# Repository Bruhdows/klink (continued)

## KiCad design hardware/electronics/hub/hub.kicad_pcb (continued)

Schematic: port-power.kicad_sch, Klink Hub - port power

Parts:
C100, C101, C102: 1uF 50V; C_0805_2012Metric; MPN C2012X7R1H105K125AB
C103: 22nF 50V C0G; C_TDK_C2012_Reflow; MPN C2012C0G1H223J125AA
C104: 100nF 50V X7R; C_0805_2012Metric; MPN C2012X7R1H104K125AE
D100: SMBJ22A-E3/52; D_SMB; MPN SMBJ22A-E3/52
Q10: CSD19537Q3; CSD19537Q3_TI; MPN CSD19537Q3
Q11: BSS138LT1G; SOT-23; MPN BSS138LT1G
R100: 10m 1% 1W; R_Vishay_WSL2512_10m; MPN WSL2512R0100FEA
R101, R106, R108: 10k 0.1%; R_0805_2012Metric; MPN TNPW080510K0BEEA
R102: 3k 0.1%; R_0805_2012Metric; MPN TNPW08053K00BEEA
R103, R104: 22k 1%; R_0805_2012Metric; MPN RC0805FR-0722KL
R105: 130k 0.1%; R_0805_2012Metric; MPN TNPW0805130KBEEA
R107: 172k 0.1%; R_0805_2012Metric; MPN TNPW0805172KBEEA
R109: 10k 1%; R_0805_2012Metric; MPN RC0805FR-0710KL
R110: 10k 1% 0.25W; R_1206_3216Metric; MPN RC1206FR0710KL
U20: TPS26630RGER; Texas_RGE0024H_VQFN-24-1EP_4x4mm_P0.5mm_EP2.7x2.7mm_Thermal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; MPN TPS26630RGER
U21: INA301A1IDGKR; VSSOP-8_3x3mm_P0.65mm; MPN INA301A1IDGKR

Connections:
/Distribution/PORT1_20V: C102.1, D100.1 (K), R105.1, R110.1, U20.17 (OUT), U20.18 (OUT); also elsewhere on the board
/Distribution/Port 1/B_DRV: Q11.1 (G), U20.4 (DRV)
/Distribution/Port 1/B_GATE: Q10.4 (G), Q11.3 (D), U20.3 (B_GATE)
/Distribution/Port 1/EFUSE_IN: C101.1, Q10.5 (D), U20.1 (IN), U20.2 (IN)
/Distribution/Port 1/PORT_DVDT: C103.1, U20.9 (dVdT)
/Distribution/Port 1/PORT_ILIM: R102.1, U20.10 (ILIM)
/Distribution/Port 1/PORT_IN: C100.1, Q10.1 (S), Q10.2 (S), Q10.3 (S), Q11.2 (S), R100.2, R107.1, U20.5 (IN_SYS), U21.7 (IN-)
/Distribution/Port 1/PORT_LIMIT: R101.1, U21.3 (LIMIT)
/Distribution/Port 1/PORT_OVP: R107.2, R108.1, U20.7 (OVP)
/Distribution/Port 1/PORT_PGTH: R105.2, R106.1, U20.15 (PGTH)
/INPUT_ENABLE: R109.1, U20.12 (~SHDN); also elsewhere on the board
CONTROL_3V3: C104.1, R103.1, R104.1, U21.1 (VS); also elsewhere on the board
CONTROL_GOOD: U21.5 (RESET); also elsewhere on the board
GND: C100.2, C101.2, C102.2, C103.2, C104.2, D100.2 (A), R101.2, R102.2, R106.2, R108.2, R109.2, R110.2, U20.6 (UVLO), U20.8 (GND), U20.25 (GND), U21.4 (GND); also elsewhere on the board
HUB_20V: R100.1, U21.8 (IN+); also elsewhere on the board
PORT1_HEALTH_N: R104.2, U20.14 (~FLT), U20.16 (PGOOD); also elsewhere on the board
PORT1_MON: U21.2 (OUT); also elsewhere on the board
PORT1_OC_N: R103.2, U21.6 (~ALERT); also elsewhere on the board

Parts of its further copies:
C110, C111, C112, C120, C121, C122, C130, C131, C132, C140, C141, C142, C150, C151, C152: 1uF 50V; C_0805_2012Metric; MPN C2012X7R1H105K125AB
C113, C123, C133, C143, C153: 22nF 50V C0G; C_TDK_C2012_Reflow; MPN C2012C0G1H223J125AA
C114, C124, C134, C144, C154: 100nF 50V X7R; C_0805_2012Metric; MPN C2012X7R1H104K125AE
D101, D102, D103, D104, D105: SMBJ22A-E3/52; D_SMB; MPN SMBJ22A-E3/52
Q12, Q14, Q16, Q18, Q20: CSD19537Q3; CSD19537Q3_TI; MPN CSD19537Q3
Q13, Q15, Q17, Q19, Q21: BSS138LT1G; SOT-23; MPN BSS138LT1G
R120, R140, R160, R180, R200: 10m 1% 1W; R_Vishay_WSL2512_10m; MPN WSL2512R0100FEA
R121, R126, R128, R141, R146, R148, R161, R166, R168, R181, R186, R188, R201, R206, R208: 10k 0.1%; R_0805_2012Metric; MPN TNPW080510K0BEEA
R122, R142, R162, R182, R202: 3k 0.1%; R_0805_2012Metric; MPN TNPW08053K00BEEA
R123, R124, R143, R144, R163, R164, R183, R184, R203, R204: 22k 1%; R_0805_2012Metric; MPN RC0805FR-0722KL
R125, R145, R165, R185, R205: 130k 0.1%; R_0805_2012Metric; MPN TNPW0805130KBEEA
R127, R147, R167, R187, R207: 172k 0.1%; R_0805_2012Metric; MPN TNPW0805172KBEEA
R129, R149, R169, R189, R209: 10k 1%; R_0805_2012Metric; MPN RC0805FR-0710KL
R130, R150, R170, R190, R210: 10k 1% 0.25W; R_1206_3216Metric; MPN RC1206FR0710KL
U22, U24, U26, U28, U30: TPS26630RGER; Texas_RGE0024H_VQFN-24-1EP_4x4mm_P0.5mm_EP2.7x2.7mm_Thermal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; MPN TPS26630RGER
U23, U25, U27, U29, U31: INA301A1IDGKR; VSSOP-8_3x3mm_P0.65mm; MPN INA301A1IDGKR

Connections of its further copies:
/Distribution/PORT2_20V: C112.1, D101.1 (K), R125.1, R130.1, U22.17 (OUT), U22.18 (OUT); also elsewhere on the board
/Distribution/PORT3_20V: C122.1, D102.1 (K), R145.1, R150.1, U24.17 (OUT), U24.18 (OUT); also elsewhere on the board
/Distribution/PORT4_20V: C132.1, D103.1 (K), R165.1, R170.1, U26.17 (OUT), U26.18 (OUT); also elsewhere on the board
/Distribution/PORT5_20V: C142.1, D104.1 (K), R185.1, R190.1, U28.17 (OUT), U28.18 (OUT); also elsewhere on the board
/Distribution/PORT6_20V: C152.1, D105.1 (K), R205.1, R210.1, U30.17 (OUT), U30.18 (OUT); also elsewhere on the board
/Distribution/Port 2/B_DRV: Q13.1 (G), U22.4 (DRV)
/Distribution/Port 2/B_GATE: Q12.4 (G), Q13.3 (D), U22.3 (B_GATE)
/Distribution/Port 2/EFUSE_IN: C111.1, Q12.5 (D), U22.1 (IN), U22.2 (IN)
/Distribution/Port 2/PORT_DVDT: C113.1, U22.9 (dVdT)
/Distribution/Port 2/PORT_ILIM: R122.1, U22.10 (ILIM)
/Distribution/Port 2/PORT_IN: C110.1, Q12.1 (S), Q12.2 (S), Q12.3 (S), Q13.2 (S), R120.2, R127.1, U22.5 (IN_SYS), U23.7 (IN-)
/Distribution/Port 2/PORT_LIMIT: R121.1, U23.3 (LIMIT)
/Distribution/Port 2/PORT_OVP: R127.2, R128.1, U22.7 (OVP)
/Distribution/Port 2/PORT_PGTH: R125.2, R126.1, U22.15 (PGTH)
/Distribution/Port 3/B_DRV: Q15.1 (G), U24.4 (DRV)
/Distribution/Port 3/B_GATE: Q14.4 (G), Q15.3 (D), U24.3 (B_GATE)
/Distribution/Port 3/EFUSE_IN: C121.1, Q14.5 (D), U24.1 (IN), U24.2 (IN)
/Distribution/Port 3/PORT_DVDT: C123.1, U24.9 (dVdT)
/Distribution/Port 3/PORT_ILIM: R142.1, U24.10 (ILIM)
/Distribution/Port 3/PORT_IN: C120.1, Q14.1 (S), Q14.2 (S), Q14.3 (S), Q15.2 (S), R140.2, R147.1, U24.5 (IN_SYS), U25.7 (IN-)
/Distribution/Port 3/PORT_LIMIT: R141.1, U25.3 (LIMIT)
/Distribution/Port 3/PORT_OVP: R147.2, R148.1, U24.7 (OVP)
/Distribution/Port 3/PORT_PGTH: R145.2, R146.1, U24.15 (PGTH)
/Distribution/Port 4/B_DRV: Q17.1 (G), U26.4 (DRV)
/Distribution/Port 4/B_GATE: Q16.4 (G), Q17.3 (D), U26.3 (B_GATE)
/Distribution/Port 4/EFUSE_IN: C131.1, Q16.5 (D), U26.1 (IN), U26.2 (IN)
/Distribution/Port 4/PORT_DVDT: C133.1, U26.9 (dVdT)
/Distribution/Port 4/PORT_ILIM: R162.1, U26.10 (ILIM)
/Distribution/Port 4/PORT_IN: C130.1, Q16.1 (S), Q16.2 (S), Q16.3 (S), Q17.2 (S), R160.2, R167.1, U26.5 (IN_SYS), U27.7 (IN-)
/Distribution/Port 4/PORT_LIMIT: R161.1, U27.3 (LIMIT)
/Distribution/Port 4/PORT_OVP: R167.2, R168.1, U26.7 (OVP)
/Distribution/Port 4/PORT_PGTH: R165.2, R166.1, U26.15 (PGTH)
/Distribution/Port 5/B_DRV: Q19.1 (G), U28.4 (DRV)
/Distribution/Port 5/B_GATE: Q18.4 (G), Q19.3 (D), U28.3 (B_GATE)
/Distribution/Port 5/EFUSE_IN: C141.1, Q18.5 (D), U28.1 (IN), U28.2 (IN)
/Distribution/Port 5/PORT_DVDT: C143.1, U28.9 (dVdT)
/Distribution/Port 5/PORT_ILIM: R182.1, U28.10 (ILIM)
/Distribution/Port 5/PORT_IN: C140.1, Q18.1 (S), Q18.2 (S), Q18.3 (S), Q19.2 (S), R180.2, R187.1, U28.5 (IN_SYS), U29.7 (IN-)
/Distribution/Port 5/PORT_LIMIT: R181.1, U29.3 (LIMIT)
/Distribution/Port 5/PORT_OVP: R187.2, R188.1, U28.7 (OVP)
/Distribution/Port 5/PORT_PGTH: R185.2, R186.1, U28.15 (PGTH)
/Distribution/Port 6/B_DRV: Q21.1 (G), U30.4 (DRV)
/Distribution/Port 6/B_GATE: Q20.4 (G), Q21.3 (D), U30.3 (B_GATE)
/Distribution/Port 6/EFUSE_IN: C151.1, Q20.5 (D), U30.1 (IN), U30.2 (IN)
/Distribution/Port 6/PORT_DVDT: C153.1, U30.9 (dVdT)
/Distribution/Port 6/PORT_ILIM: R202.1, U30.10 (ILIM)
/Distribution/Port 6/PORT_IN: C150.1, Q20.1 (S), Q20.2 (S), Q20.3 (S), Q21.2 (S), R200.2, R207.1, U30.5 (IN_SYS), U31.7 (IN-)
/Distribution/Port 6/PORT_LIMIT: R201.1, U31.3 (LIMIT)
/Distribution/Port 6/PORT_OVP: R207.2, R208.1, U30.7 (OVP)
/Distribution/Port 6/PORT_PGTH: R205.2, R206.1, U30.15 (PGTH)
/INPUT_ENABLE: R129.1, R149.1, R169.1, R189.1, R209.1, U22.12 (~SHDN), U24.12 (~SHDN), U26.12 (~SHDN), U28.12 (~SHDN), U30.12 (~SHDN); also elsewhere on the board
CONTROL_3V3: C114.1, C124.1, C134.1, C144.1, C154.1, R123.1, R124.1, R143.1, R144.1, R163.1, R164.1, R183.1, R184.1, R203.1, R204.1, U23.1 (VS), U25.1 (VS), U27.1 (VS), U29.1 (VS), U31.1 (VS); also elsewhere on the board
CONTROL_GOOD: U23.5 (RESET), U25.5 (RESET), U27.5 (RESET), U29.5 (RESET), U31.5 (RESET); also elsewhere on the board
GND: C110.2, C111.2, C112.2, C113.2, C114.2, C120.2, C121.2, C122.2, C123.2, C124.2, C130.2, C131.2, C132.2, C133.2, C134.2, C140.2, C141.2, C142.2, C143.2, C144.2, C150.2, C151.2, C152.2, C153.2, C154.2, D101.2 (A), D102.2 (A), D103.2 (A), D104.2 (A), D105.2 (A), R121.2, R122.2, R126.2, R128.2, R129.2, R130.2, R141.2, R142.2, R146.2, R148.2, R149.2, R150.2, R161.2, R162.2, R166.2, R168.2, R169.2, R170.2, R181.2, R182.2, R186.2, R188.2, R189.2, R190.2, R201.2, R202.2, R206.2, R208.2, R209.2, R210.2, U22.6 (UVLO), U22.8 (GND), U22.25 (GND), U23.4 (GND), U24.6 (UVLO), U24.8 (GND), U24.25 (GND), U25.4 (GND), U26.6 (UVLO), U26.8 (GND), U26.25 (GND), U27.4 (GND), U28.6 (UVLO), U28.8 (GND), U28.25 (GND), U29.4 (GND), U30.6 (UVLO), U30.8 (GND), U30.25 (GND), U31.4 (GND); also elsewhere on the board
HUB_20V: R120.1, R140.1, R160.1, R180.1, R200.1, U23.8 (IN+), U25.8 (IN+), U27.8 (IN+), U29.8 (IN+), U31.8 (IN+); also elsewhere on the board
PORT2_HEALTH_N: R124.2, U22.14 (~FLT), U22.16 (PGOOD); also elsewhere on the board
PORT2_MON: U23.2 (OUT); also elsewhere on the board
PORT2_OC_N: R123.2, U23.6 (~ALERT); also elsewhere on the board
PORT3_HEALTH_N: R144.2, U24.14 (~FLT), U24.16 (PGOOD); also elsewhere on the board
PORT3_MON: U25.2 (OUT); also elsewhere on the board
PORT3_OC_N: R143.2, U25.6 (~ALERT); also elsewhere on the board
PORT4_HEALTH_N: R164.2, U26.14 (~FLT), U26.16 (PGOOD); also elsewhere on the board
PORT4_MON: U27.2 (OUT); also elsewhere on the board
PORT4_OC_N: R163.2, U27.6 (~ALERT); also elsewhere on the board
PORT5_HEALTH_N: R184.2, U28.14 (~FLT), U28.16 (PGOOD); also elsewhere on the board
PORT5_MON: U29.2 (OUT); also elsewhere on the board
PORT5_OC_N: R183.2, U29.6 (~ALERT); also elsewhere on the board
PORT6_HEALTH_N: R204.2, U30.14 (~FLT), U30.16 (PGOOD); also elsewhere on the board
PORT6_MON: U31.2 (OUT); also elsewhere on the board
PORT6_OC_N: R203.2, U31.6 (~ALERT); also elsewhere on the board

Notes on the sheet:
Kelvin route R100. Nominal trip 4A; all ports latch off on a fault.
C100-C102 require at least 0.1uF effective capacitance at 21V.
TVS clamp is 35.5V at 16.9A, 25C. Hot-pulse coordination remains unqualified.

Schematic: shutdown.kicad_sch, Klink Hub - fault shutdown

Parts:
C300, C303, C306, C307, C308, C309, C310, C311, C312, C313: 100nF 50V X7R; C_0805_2012Metric; MPN C2012X7R1H104K125AE
R302: 22k 1%; R_0805_2012Metric; MPN RC0805FR-0722KL
R303: 100k 1%; R_0805_2012Metric; MPN RC0805FR-07100KL
R304: 47k 1%; R_0805_2012Metric; MPN RC0805FR-0747KL
TP30: FAULT_LATCHED; TestPoint_Pad_D2.0mm
TP31: ARMED; TestPoint_Pad_D2.0mm
U40, U43: SN74HCS11PWR; TSSOP-14_4.4x5mm_P0.65mm; MPN SN74HCS11PWR
U46, U48: SN74LVC1G32DBVR; SOT-23-5; MPN SN74LVC1G32DBVR
U47: SN74LVC1G08DBVR; SOT-23-5; MPN SN74LVC1G08DBVR
U49: SN74LVC1G04DBVR; SOT-23-5; MPN SN74LVC1G04DBVR
U50: SN74LVC74APWR; TSSOP-14_4.4x5mm_P0.65mm; MPN SN74LVC74APWR
U51, U53: SN74LVC2G17DBVR; SOT-23-6; MPN SN74LVC2G17DBVR
U52: TPS3808G01DBVR; SOT-23-6; MPN TPS3808G01DBVR

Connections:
/CONTROL_GOOD_RAW: U51.3; also elsewhere on the board
/Distribution/Fault shutdown/ALL_HEALTH_N: U46.1, U53.4
/Distribution/Fault shutdown/ALL_HEALTH_RAW_N: U43.8, U53.3
/Distribution/Fault shutdown/ALL_OC_N: U47.1, U53.6
/Distribution/Fault shutdown/ALL_OC_RAW_N: U40.8, U53.1
/Distribution/Fault shutdown/ARM_N: U46.2, U50.8 (~Q)
/Distribution/Fault shutdown/CONTROL_GOOD_N: U48.2, U49.4
/Distribution/Fault shutdown/FAULT_SET_N: U48.4, U50.4 (~S)
/Distribution/Fault shutdown/FAULT_SOURCE_N: U47.4, U48.1
/Distribution/Fault shutdown/HEALTH_A: U43.9, U43.12
/Distribution/Fault shutdown/HEALTH_B: U43.6, U43.10
/Distribution/Fault shutdown/HEALTH_READY_N: U46.4, U47.2
/Distribution/Fault shutdown/OC_A: U40.9, U40.12
/Distribution/Fault shutdown/OC_B: U40.6, U40.10
/Distribution/Fault shutdown/START_CT: R303.2, U52.4 (CT)
/Distribution/Fault shutdown/START_DONE: U50.11 (C), U51.6
/Distribution/Fault shutdown/START_DONE_RAW: R302.2, U51.1, U52.1 (~RESET)
/INPUT_ENABLE: U52.5 (SENSE); also elsewhere on the board
/RUN_OK: R304.1, U50.6 (~Q); also elsewhere on the board
ARMED: TP31.1, U50.9 (Q); also elsewhere on the board
CONTROL_3V3: C300.1, C303.1, C306.1, C307.1, C308.1, C309.1, C310.1, C311.1, C312.1, C313.1, R302.1, R303.1, U40.14 (VCC), U43.14 (VCC), U46.5 (VCC), U47.5 (VCC), U48.5 (VCC), U49.5 (VCC), U50.10 (~S), U50.12 (D), U50.14 (VCC), U51.5 (VCC), U52.6 (VDD), U53.5 (VCC); also elsewhere on the board
CONTROL_GOOD: U49.2, U50.1 (~R), U50.13 (~R), U51.4, U52.3 (~MR); also elsewhere on the board
FAULT_LATCHED: TP30.1, U50.5 (Q); also elsewhere on the board
GND: C300.2, C303.2, C306.2, C307.2, C308.2, C309.2, C310.2, C311.2, C312.2, C313.2, R304.2, U40.7 (GND), U43.7 (GND), U46.3 (GND), U47.3 (GND), U48.3 (GND), U49.3 (GND), U50.2 (D), U50.3 (C), U50.7 (GND), U51.2 (GND), U52.2 (GND), U53.2 (GND); also elsewhere on the board
INPUT_FAULT_N: U43.11; also elsewhere on the board
INPUT_OC_N: U40.11; also elsewhere on the board
PORT1_HEALTH_N: U43.1; also elsewhere on the board
PORT1_OC_N: U40.1; also elsewhere on the board
PORT2_HEALTH_N: U43.2; also elsewhere on the board
PORT2_OC_N: U40.2; also elsewhere on the board
PORT3_HEALTH_N: U43.13; also elsewhere on the board
PORT3_OC_N: U40.13; also elsewhere on the board
PORT4_HEALTH_N: U43.3; also elsewhere on the board
PORT4_OC_N: U40.3; also elsewhere on the board
PORT5_HEALTH_N: U43.4; also elsewhere on the board
PORT5_OC_N: U40.4; also elsewhere on the board
PORT6_HEALTH_N: U43.5; also elsewhere on the board
PORT6_OC_N: U40.5; also elsewhere on the board

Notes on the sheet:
Overcurrent is never blanked. Health faults latch when the startup allowance expires.
CT to VDD through 100k: 180-420ms allowance from the power-enable request.

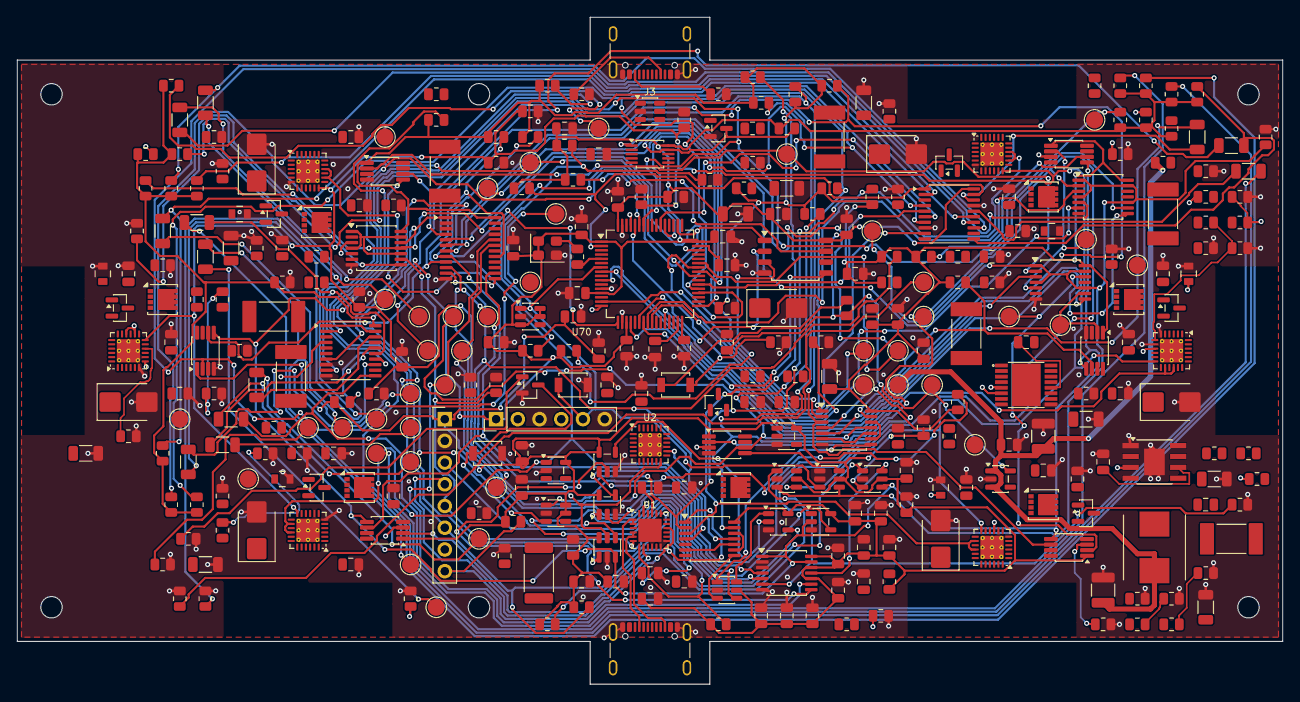
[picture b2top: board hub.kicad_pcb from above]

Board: 4 copper layers, 148.0 x 78.0 mm, 356 parts (0 on the bottom side), 227 nets.

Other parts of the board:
H1, H2, H3, H4, H5, H6: MountingHole_2.5mm

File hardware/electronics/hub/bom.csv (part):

Reference,Value,MPN,Alternate,TCR,Footprint,Quantity,purchase_url,unit_price,currency,price_status,checked_date,lcsc_reference
C1,1uF 50V,C2012X7R1H105K125AB,,,Capacitor_SMD:C_0805_2012Metric,1,https://www.mouser.com/ProductDetail/TDK/C2012X7R1H105K125AB,0.1,USD,engineering allowance; NOT a verified supplier price,,
C2,1uF 10V,C2012X7R1H105K125AB,,,Capacitor_SMD:C_0805_2012Metric,1,https://www.mouser.com/ProductDetail/TDK/C2012X7R1H105K125AB,0.1,USD,engineering allowance; NOT a verified supplier price,,
C3,1uF 10V,C2012X7R1H105K125AB,,,Capacitor_SMD:C_0805_2012Metric,1,https://www.mouser.com/ProductDetail/TDK/C2012X7R1H105K125AB,0.1,USD,engineering allowance; NOT a verified supplier price,,
C4,100nF 50V X7R,C2012X7R1H104K125AE,,,Capacitor_SMD:C_0805_2012Metric,1,https://www.mouser.com/ProductDetail/TDK/C2012X7R1H104K125AE,0.1,USD,engineering allowance; NOT a verified supplier price,,
J1,USB4105-GF-A,USB4105-GF-A,,,Klink:USB_C_Receptacle_GCT_USB4105_RoundedGround,1,https://www.mouser.com/ProductDetail/GCT/USB4105-GF-A,0.9,USD,engineering allowance; NOT a verified supplier price,,
J2,PD_SERVICE,TSW-108-07-G-S,,,Connector_PinHeader_2.54mm:PinHeader_1x08_P2.54mm_Vertical,1,https://www.mouser.com/ProductDetail/Samtec/TSW-108-07-G-S,0.7,USD,engineering allowance; NOT a verified supplier price,,
R1,470 1% 2W,RC2512FK-7W470RL,,,Resistor_SMD:R_2512_6332Metric,1,https://www.mouser.com/ProductDetail/Yageo/RC2512FK-7W470RL,0.1,USD,engineering allowance; NOT a verified supplier price,,
R2,10k 1%,RC0805FR-0710KL,,,Resistor_SMD:R_0805_2012Metric,1,https://www.lcsc.com/product-detail/C84376.html,0.0049,USD,supplier reference listing; not a quote,2026-11-08,C84376
R3,4.7k 1%,RC0805FR-074K7L,,,Resistor_SMD:R_0805_2012Metric,1,https://www.mouser.com/ProductDetail/Yageo/RC0805FR-074K7L,0.04,USD,engineering allowance; NOT a verified supplier price,,
R4,4.7k 1%,RC0805FR-074K7L,,,Resistor_SMD:R_0805_2012Metric,1,https://www.mouser.com/ProductDetail/Yageo/RC0805FR-074K7L,0.04,USD,engineering allowance; NOT a verified supplier price,,
R5,4.7k 1%,RC0805FR-074K7L,,,Resistor_SMD:R_0805_2012Metric,1,https://www.mouser.com/ProductDetail/Yageo/RC0805FR-074K7L,0.04,USD,engineering allowance; NOT a verified supplier price,,
R6,10k 1%,RC0805FR-0710KL,,,Resistor_SMD:R_0805_2012Metric,1,https://www.lcsc.com/product-detail/C84376.html,0.0049,USD,supplier reference listing; not a quote,2026-11-08,C84376
R7,10k 1%,RC0805FR-0710KL,,,Resistor_SMD:R_0805_2012Metric,1,https://www.lcsc.com/product-detail/C84376.html,0.0049,USD,supplier reference listing; not a quote,2026-11-08,C84376
U1,STUSB4500QTR,STUSB4500QTR,,,Package_DFN_QFN:QFN-24-1EP_4x4mm_P0.5mm_EP2.7x2.7mm,1,https://www.mouser.com/ProductDetail/STMicroelectronics/STUS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,3,USD,engineering allowance; NOT a verified supplier price,,
C5,100nF 50V X7R,C2012X7R1H104K125AE,,,Capacitor_SMD:C_0805_2012Metric,1,https://www.mouser.com/ProductDetail/TDK/C2012X7R1H104K125AE,0.1,USD,engineering allowance; NOT a verified supplier price,,
C6,1uF 50V,C2012X7R1H105K125AB,,,Capacitor_SMD:C_0805_2012Metric,1,https://www.mouser.com/ProductDetail/TDK/C2012X7R1H105K125AB,0.1,USD,engineering allowance; NOT a verified supplier price,,
C7,100nF 50V X7R,C2012X7R1H104K125AE,,,Capacitor_SMD:C_0805_2012Metric,1,https://www.mouser.com/ProductDetail/TDK/C2012X7R1H104K125AE,0.1,USD,engineering allowance; NOT a verified supplier price,,
C8,100nF 50V,C2012X7R1H104K125AE,,,Capacitor_SMD:C_0805_2012Metric,1,https://www.mouser.com/ProductDetail/TDK/C2012X7R1H104K125AE,0.1,USD,engineering allowance; NOT a verified supplier price,,
C9,10uF 50V X7R,C3216X7R1H106K160AC,,,Capacitor_SMD:C_1206_3216Metric,1,https://www.mouser.com/ProductDetail/TDK/C3216X7R1H106K160AC,0.35,USD,engineering allowance; NOT a verified supplier price,,
C10,100nF 50V X7R,C2012X7R1H104K125AE,,,Capacitor_SMD:C_0805_2012Metric,1,https://www.mouser.com/ProductDetail/TDK/C2012X7R1H104K125AE,0.1,USD,engineering allowance; NOT a verified supplier price,,
C11,100nF 50V X7R,C2012X7R1H104K125AE,,,Capacitor_SMD:C_0805_2012Metric,1,https://www.mouser.com/ProductDetail/TDK/C2012X7R1H104K125AE,0.1,USD,engineering allowance; NOT a verified supplier price,,
C12,100nF 50V X7R,C2012X7R1H104K125AE,,,Capacitor_SMD:C_0805_2012Metric,1,https://www.mouser.com/ProductDetail/TDK/C2012X7R1H104K125AE,0.1,USD,engineering allowance; NOT a verified supplier price,,
C13,100nF 50V X7R,C2012X7R1H104K125AE,,,Capacitor_SMD:C_0805_2012Metric,1,https://www.mouser.com/ProductDetail/TDK/C2012X7R1H104K125AE,0.1,USD,engineering allowance; NOT a verified supplier price,,
C14,1uF 50V,C2012X7R1H105K125AB,,,Capacitor_SMD:C_0805_2012Metric,1,https://www.mouser.com/ProductDetail/TDK/C2012X7R1H105K125AB,0.1,USD,engineering allowance; NOT a verified supplier price,,
C462,100nF 50V X7R,C2012X7R1H104K125AE,,,Capacitor_SMD:C_0805_2012Metric,1,https://www.mouser.com/ProductDetail/TDK/C2012X7R1H104K125AE,0.1,USD,engineering allowance; NOT a verified supplier price,,
D8,SMBJ22A-E3/52,SMBJ22A-E3/52,,,Diode_SMD:D_SMB,1,https://www.mouser.com/ProductDetail/Vishay/SMBJ22A-E3%2F52,0.35,USD,engineering allowance; NOT a verified supplier price,,
Q1,CSD19537Q3,CSD19537Q3,,,Klink:CSD19537Q3_TI,1,https://www.mouser.com/ProductDetail/Texas-Instruments/CSD19537Q3,1.5,USD,engineering allowance; NOT a verified supplier price,,
Q2,BSS138LT1G,BSS138LT1G,,,Package_TO_SOT_SMD:SOT-23,1,https://www.mouser.com/ProductDetail/onsemi/BSS138LT1G,0.15,USD,engineering allowance; NOT a verified supplier price,,
R8,10m 1% 1W,WSL2512R0100FEA,,,Klink:R_Vishay_WSL2512_10m,1,https://www.mouser.com/ProductDetail/Vishay/WSL2512R0100FEA,0.7,USD,engineering allowance; NOT a verified supplier price,,
R9,135k 0.1%,TNPW0805135KBEEA,,25ppm/K,Resistor_SMD:R_0805_2012Metric,1,https://www.mouser.com/ProductDetail/Vishay/TNPW0805135KBEEA,0.3,USD,engineering allowance; NOT a verified supplier price,,
R10,10k 0.1%,TNPW080510K0BEEA,,25ppm/K,Resistor_SMD:R_0805_2012Metric,1,https://www.mouser.com/ProductDetail/Vishay/TNPW080510K0BEEA,0.3,USD,engineering allowance; NOT a verified supplier price,,
R11,172k 0.1%,TNPW0805172KBEEA,,25ppm/K,Resistor_SMD:R_0805_2012Metric,1,https://www.mouser.com/ProductDetail/Vishay/TNPW0805172KBEEA,0.3,USD,engineering allowance; NOT a verified supplier price,,
R12,10k 0.1%,TNPW080510K0BEEA,,25ppm/K,Resistor_SMD:R_0805_2012Metric,1,https://www.mouser.com/ProductDetail/Vishay/TNPW080510K0BEEA,0.3,USD,engineering allowance; NOT a verified supplier price,,
R13,3k 0.1%,TNPW08053K00BEEA,,25ppm/K,Resistor_SMD:R_0805_2012Metric,1,https://www.mouser.com/ProductDetail/Vishay/TNPW08053K00BEEA,0.3,USD,engineering allowance; NOT a verified supplier price,,
R14,10.5k 0.1%,ERA6AEB1052V,,25ppm/K,Resistor_SMD:R_0805_2012Metric,1,https://www.mouser.com/ProductDetail/Panasonic/ERA6AEB1052V,0.3,USD,engineering allowance; NOT a verified supplier price,,
R15,22k 1%,RC0805FR-0722KL,,,Resistor_SMD:R_0805_2012Metric,1,https://www.mouser.com/ProductDetail/Yageo/RC0805FR-0722KL,0.04,USD,engineering allowance; NOT a verified supplier price,,
R16,10k 1%,RC0805FR-0710KL,,,Resistor_SMD:R_0805_2012Metric,1,https://www.lcsc.com/product-detail/C84376.html,0.0049,USD,supplier reference listing; not a quote,2026-11-08,C84376
R17,10k 1%,RC0805FR-0710KL,,,Resistor_SMD:R_0805_2012Metric,1,https://www.lcsc.com/product-detail/C84376.html,0.0049,USD,supplier reference listing; not a quote,2026-11-08,C84376
R18,10k 1%,RC0805FR-0710KL,,,Resistor_SMD:R_0805_2012Metric,1,https://www.lcsc.com/product-detail/C84376.html,0.0049,USD,supplier reference listing; not a quote,2026-11-08,C84376
R19,22k 1%,RC0805FR-0722KL,,,Resistor_SMD:R_0805_2012Metric,1,https://www.mouser.com/ProductDetail/Yageo/RC0805FR-0722KL,0.04,USD,engineering allowance; NOT a verified supplier price,,
R20,10k 1% 0.25W,RC1206FR0710KL,,,Resistor_SMD:R_1206_3216Metric,1,https://www.mouser.com/ProductDetail/Yageo/RC1206FR0710KL,0.1,USD,engineering allowance; NOT a verified supplier price,,
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
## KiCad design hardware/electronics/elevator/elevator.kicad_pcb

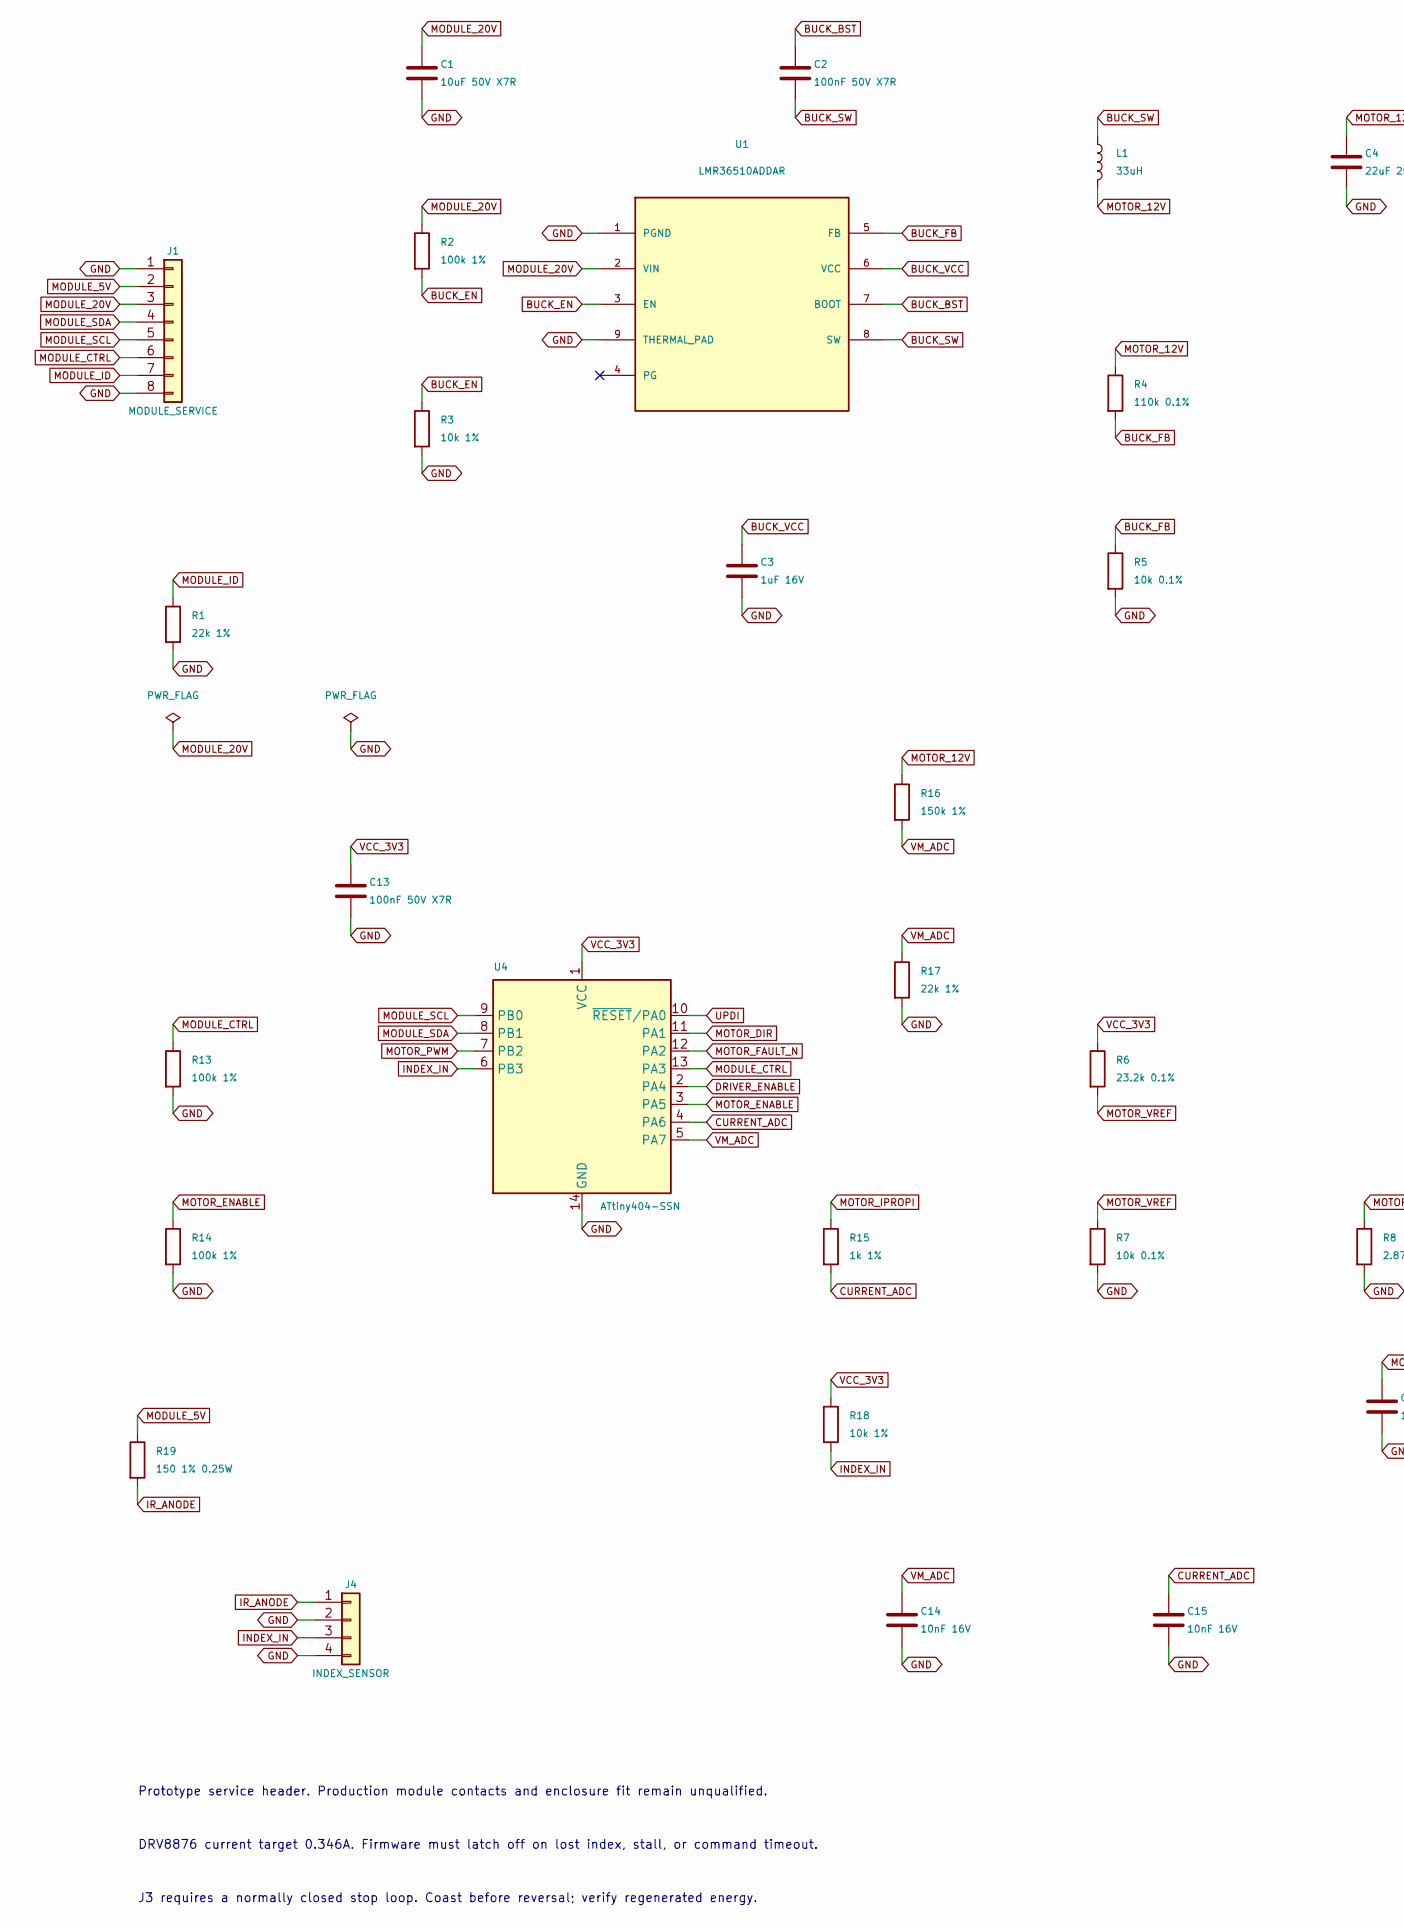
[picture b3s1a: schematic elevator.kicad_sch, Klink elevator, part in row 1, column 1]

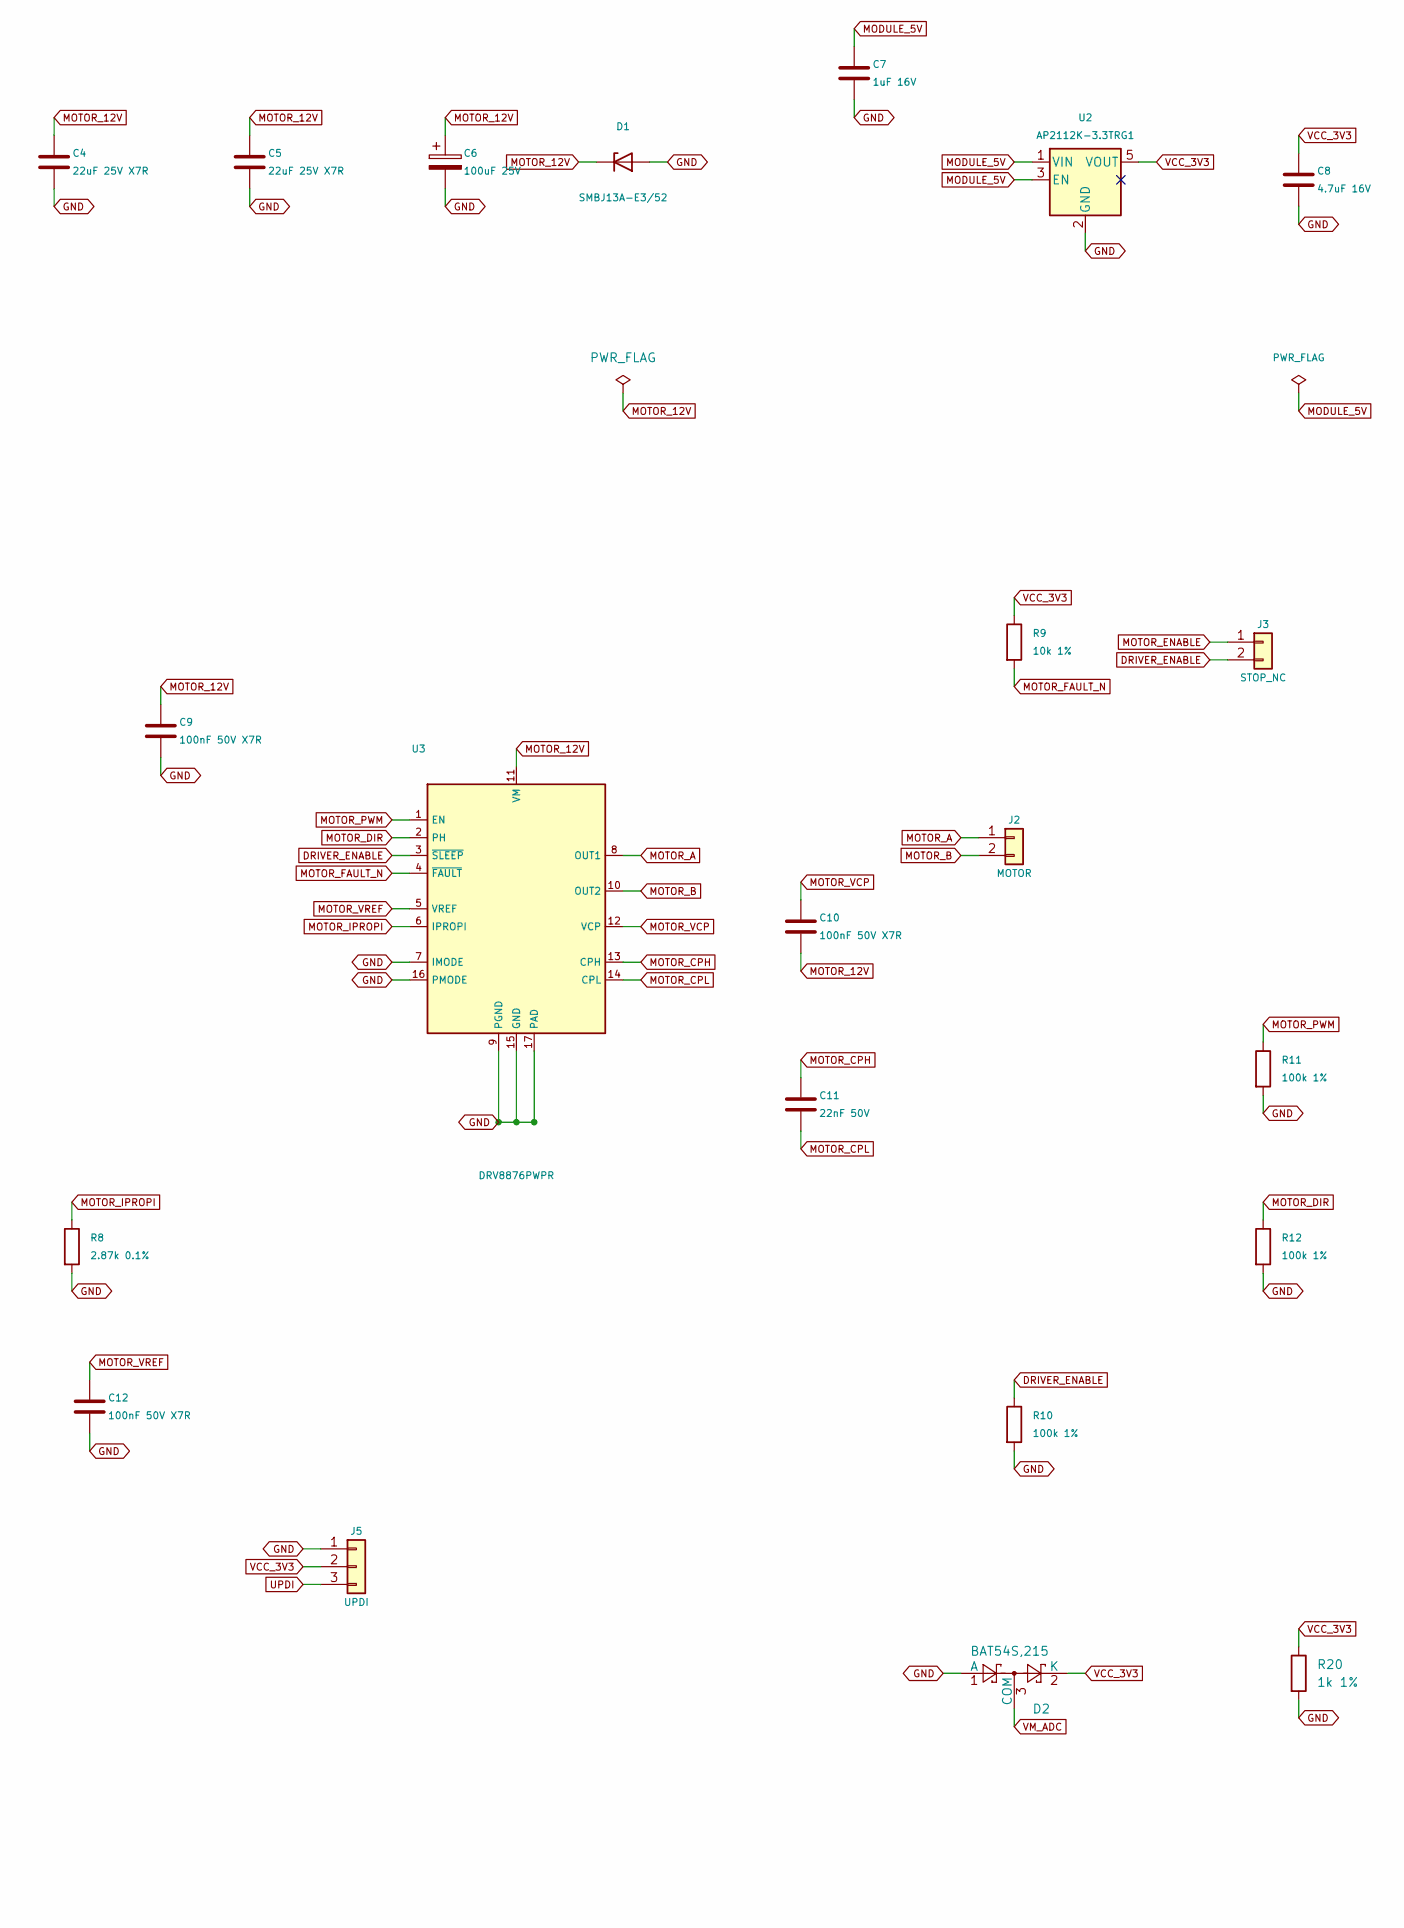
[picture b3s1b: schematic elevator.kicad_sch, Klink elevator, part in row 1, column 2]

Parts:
C1: 10uF 50V X7R; C_1206_3216Metric; MPN C3216X7R1H106K160AC
C2, C9, C10, C12, C13: 100nF 50V X7R; C_0805_2012Metric; MPN C2012X7R1H104K125AE
C3, C7: 1uF 16V; C_0805_2012Metric; MPN C2012X7R1H105K125AB
C4, C5: 22uF 25V X7R; C_1210_3225Metric; MPN C1210C226K3RACTU
C6: 100uF 25V; CP_Elec_6.3x7.7; MPN EEH-ZC1E101XP
C8: 4.7uF 16V; C_0805_2012Metric; MPN C2012X7R1C475K125AB
C11: 22nF 50V; C_TDK_C2012_Reflow; MPN C2012C0G1H223J125AA
C14, C15: 10nF 16V; C_0805_2012Metric; MPN CC0805KRX7R9BB103
D1: SMBJ13A-E3/52; D_SMB; MPN SMBJ13A-E3/52
D2: BAT54S,215; SOT-23; MPN BAT54S,215
J1: MODULE_SERVICE; PinHeader_1x08_P2.54mm_Vertical; MPN TSW-108-07-G-S
J2: MOTOR; PinHeader_1x02_P2.54mm_Vertical; MPN TSW-102-07-G-S
J3: STOP_NC; PinHeader_1x02_P2.54mm_Vertical; MPN TSW-102-07-G-S
J4: INDEX_SENSOR; PinHeader_1x04_P2.54mm_Vertical; MPN TSW-104-07-G-S
J5: UPDI; PinHeader_1x03_P2.54mm_Vertical; MPN TSW-103-07-G-S
L1: 33uH; L_Bourns_SRP7050TA; MPN SRP7050TA-330M
R1, R17: 22k 1%; R_0805_2012Metric; MPN RC0805FR-0722KL
R2, R10, R11, R12, R13, R14: 100k 1%; R_0805_2012Metric; MPN RC0805FR-07100KL
R3, R9, R18: 10k 1%; R_0805_2012Metric; MPN RC0805FR-0710KL
R4: 110k 0.1%; R_0805_2012Metric; MPN RT0805BRD07110KL
R5, R7: 10k 0.1%; R_0805_2012Metric; MPN RT0805BRD0710KL
R6: 23.2k 0.1%; R_0805_2012Metric; MPN RT0805BRD0723K2L
R8: 2.87k 0.1%; R_0805_2012Metric; MPN RT0805BRD072K87L
R15, R20: 1k 1%; R_0805_2012Metric; MPN RC0805FR-071KL
R16: 150k 1%; R_0805_2012Metric; MPN RC0805FR-07150KL
R19: 150 1% 0.25W; R_1206_3216Metric; MPN RC1206FR-07150RL
U1: LMR36510ADDAR; TI_SO-PowerPAD-8; MPN LMR36510ADDAR
U2: AP2112K-3.3TRG1; SOT-23-5; MPN AP2112K-3.3TRG1
U3: DRV8876PWPR; TI_PWP0016A_Mask3.3x3.3; MPN DRV8876PWPR
U4: ATtiny404-SSN; SOIC-14_3.9x8.7mm_P1.27mm; MPN ATTINY404-SSN

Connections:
BUCK_BST: C2.1, U1.7 (BOOT)
BUCK_EN: R2.2, R3.1, U1.3 (EN)
BUCK_FB: R4.2, R5.1, U1.5 (FB)
BUCK_SW: C2.2, L1.1, U1.8 (SW)
BUCK_VCC: C3.1, U1.6 (VCC)
CURRENT_ADC: C15.1, R15.2, U4.4 (PA6)
DRIVER_ENABLE: J3.2, R10.1, U3.3 (~SLEEP), U4.2 (PA4)
GND: C1.2, C3.2, C4.2, C5.2, C6.2, C7.2, C8.2, C9.2, C12.2, C13.2, C14.2, C15.2, D1.2 (A), D2.1 (A), J1.1, J1.8, J4.2, J4.4, J5.1, R1.2, R3.2, R5.2, R7.2, R8.2, R10.2, R11.2, R12.2, R13.2, R14.2, R17.2, R20.2, U1.1 (PGND), U1.9 (THERMAL_PAD), U2.2 (GND), U3.7 (IMODE), U3.9 (PGND), U3.15 (GND), U3.16 (PMODE), U3.17 (PAD), U4.14 (GND)
INDEX_IN: J4.3, R18.2, U4.6 (PB3)
IR_ANODE: J4.1, R19.2
MODULE_5V: C7.1, J1.2, R19.1, U2.1 (VIN), U2.3 (EN)
MODULE_20V: C1.1, J1.3, R2.1, U1.2 (VIN)
MODULE_CTRL: J1.6, R13.1, U4.13 (PA3)
MODULE_ID: J1.7, R1.1
MODULE_SCL: J1.5, U4.9 (PB0)
MODULE_SDA: J1.4, U4.8 (PB1)
MOTOR_12V: C4.1, C5.1, C6.1, C9.1, C10.2, D1.1 (K), L1.2, R4.1, R16.1, U3.11 (VM)
MOTOR_A: J2.1, U3.8 (OUT1)
MOTOR_B: J2.2, U3.10 (OUT2)
MOTOR_CPH: C11.1, U3.13 (CPH)
MOTOR_CPL: C11.2, U3.14 (CPL)
MOTOR_DIR: R12.1, U3.2 (PH), U4.11 (PA1)
MOTOR_ENABLE: J3.1, R14.1, U4.3 (PA5)
MOTOR_FAULT_N: R9.2, U3.4 (~FAULT), U4.12 (PA2)
MOTOR_IPROPI: R8.1, R15.1, U3.6 (IPROPI)
MOTOR_PWM: R11.1, U3.1 (EN), U4.7 (PB2)
MOTOR_VCP: C10.1, U3.12 (VCP)
MOTOR_VREF: C12.1, R6.2, R7.1, U3.5 (VREF)
UPDI: J5.3, U4.10 (~RESET/PA0)
VCC_3V3: C8.1, C13.1, D2.2 (K), J5.2, R6.1, R9.1, R18.1, R20.1, U2.5 (VOUT), U4.1 (VCC)
VM_ADC: C14.1, D2.3 (COM), R16.2, R17.1, U4.5 (PA7)

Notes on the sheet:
Prototype service header. Production module contacts and enclosure fit remain unqualified.
DRV8876 current target 0.346A. Firmware must latch off on lost index, stall, or command timeout.
J3 requires a normally closed stop loop. Coast before reversal; verify regenerated energy.
